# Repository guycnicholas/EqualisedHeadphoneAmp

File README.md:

# EqualisedHeadphoneAmp
These are the design files (Eagle, Spice, and an Excel spreadsheet) required for my Instructable: Equalised Headphone Amp

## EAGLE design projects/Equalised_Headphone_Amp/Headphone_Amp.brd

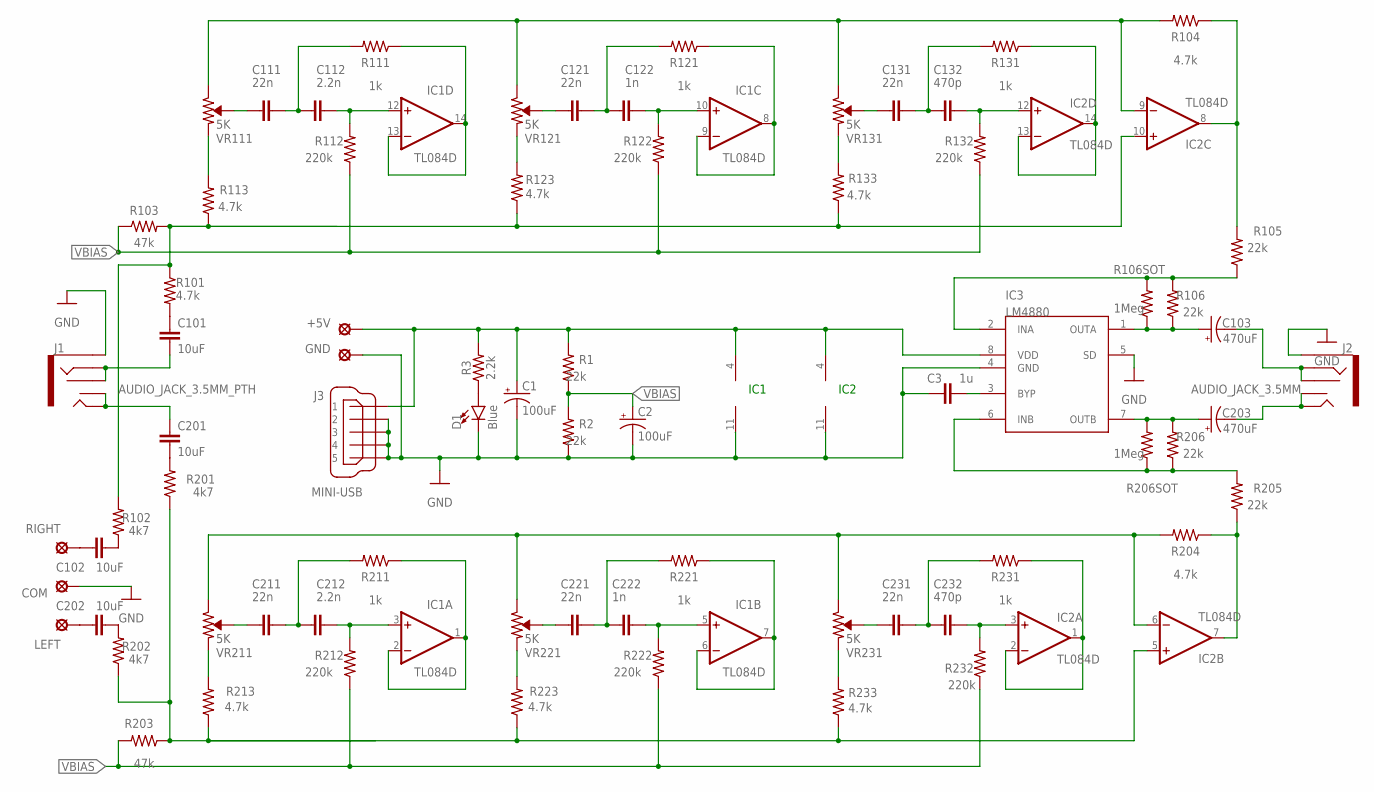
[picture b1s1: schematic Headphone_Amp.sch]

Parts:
+5V: SE14
C1, C2: 100uF; EIA7343
C3: 1u; 0603
C101, C102, C201, C202: 10uF; 0805
C103, C203: 470uF; EIA7343
C111, C121, C131, C211, C221, C231: 22n; 0603
C112, C212: 2.2n; 0603
C122, C222: 1n; 0603
C132, C232: 470p; 0603
COM: SE14
D1: Blue; LED_3MM
GND: SE14
IC1, IC2: TL084D; SO14
IC3: LM4880; SO08
J1: AUDIO_JACK_3.5MM_PTH; AUDIO-JACK
J2: AUDIO_JACK_3.5MM; AUDIO-JACK
J3: MINI-USB; UX60A-MB-5ST
LEFT: SE14
R1, R2, R105, R106, R205, R206: 22k; 0603
R3: 2.2k; 0603
R101, R104, R113, R123, R133, R204, R213, R223, R233: 4.7k; 0603
R102, R201, R202: 4k7; 0603
R103, R203: 47k; 0603
R106SOT, R206SOT: 1Meg; AXIAL-0.3
R111, R121, R131, R211, R221, R231: 1k; 0603
R112, R122, R132, R212, R222, R232: 220k; 0603
RIGHT: SE14
VR111, VR121, VR131, VR211, VR221, VR231: 5K; TRIMPOT-PTH-3362P

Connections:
GND: C1.C (-), C2.C (-), C3.1, COM.MP, D1.K (C), GND.MP, IC1.11 (V-), IC2.11 (V-), IC3.4 (GND), IC3.5 (SD), J1.SLEEVE, J2.SLEEVE, J3.2, J3.3, J3.4, J3.5, R2.1
HDPHNE: C103.C (-), J2.RING, J2.RSH
IN_L: C201.1, J1.TIP, J1.TSH
unnamed: C101.2, J1.RING, J1.RSH
unnamed: D1.A, R3.1
unnamed: C3.2, IC3.3 (BYP)
unnamed: C111.2, C112.1, R111.2
unnamed: C112.2, IC1.12 (+IN), R112.2
unnamed: IC1.1 (OUT), IC1.2 (-IN), R211.1
unnamed: C111.1, VR111.2 (WIPER)
unnamed: C203.C (-), J2.TIP, J2.TSH
unnamed: C121.2, C122.1, R121.2
unnamed: C122.2, IC1.10 (+IN), R122.2
unnamed: C201.2, R201.2
unnamed: R113.2, VR111.1 (CCW)
unnamed: C131.2, C132.1, R131.2
unnamed: C132.2, IC2.12 (+IN), R132.2
unnamed: C121.1, VR121.2 (WIPER)
unnamed: IC3.2 (INA), R105.1, R106.2, R106SOT.P$2 (2)
unnamed: C103.A (+), IC3.1 (OUTA), R106.1, R106SOT.P$1 (1)
unnamed: IC3.6 (INB), R205.2, R206.1, R206SOT.P$1 (1)
unnamed: C203.A (+), IC3.7 (OUTB), R206.2, R206SOT.P$2 (2)
unnamed: R123.2, VR121.1 (CCW)
unnamed: C211.2, C212.1, R211.2
unnamed: C212.2, IC1.3 (+IN), R212.2
unnamed: R213.2, VR211.1 (CCW)
unnamed: IC1.6 (-IN), IC1.7 (OUT), R221.1
unnamed: IC2.1 (OUT), IC2.2 (-IN), R231.1
unnamed: IC2.9 (-IN), R104.2, VR111.3 (CW), VR121.3 (CW), VR131.3 (CW)
unnamed: C221.2, C222.1, R221.2
unnamed: C222.2, IC1.5 (+IN), R222.2
unnamed: C211.1, VR211.2 (WIPER)
unnamed: IC2.6 (-IN), R204.2, VR211.3 (CW), VR221.3 (CW), VR231.3 (CW)
unnamed: C231.2, C232.1, R231.2
unnamed: C232.2, IC2.3 (+IN), R232.2
unnamed: R223.2, VR221.1 (CCW)
unnamed: IC1.8 (OUT), IC1.9 (-IN), R121.1
unnamed: R133.2, VR131.1 (CCW)
unnamed: IC2.10 (+IN), R101.1, R102.2, R103.2, R113.1, R123.1, R133.1
unnamed: +5V.MP, C1.A (+), IC1.4 (V+), IC2.4 (V+), IC3.8 (VDD), J3.1, R1.2, R3.2
unnamed: C101.1, R101.2
unnamed: IC1.13 (-IN), IC1.14 (OUT), R111.1
unnamed: C131.1, VR131.2 (WIPER)
unnamed: IC2.13 (-IN), IC2.14 (OUT), R131.1
unnamed: C221.1, VR221.2 (WIPER)
unnamed: C231.1, VR231.2 (WIPER)
unnamed: R233.2, VR231.1 (CCW)
unnamed: C102.1, RIGHT.MP
unnamed: C202.1, LEFT.MP
unnamed: C202.2, R202.2
unnamed: C102.2, R102.1
unnamed: IC2.5 (+IN), R201.1, R202.1, R203.1, R213.1, R223.1, R233.1
OUT-R: IC2.8 (OUT), R104.1, R105.2
OUT_L: IC2.7 (OUT), R204.1, R205.1
VBIAS: C2.A (+), R1.1, R2.2, R103.1, R112.1, R122.1, R132.1, R203.2, R212.1, R222.1, R232.1

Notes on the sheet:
IC1
IC2

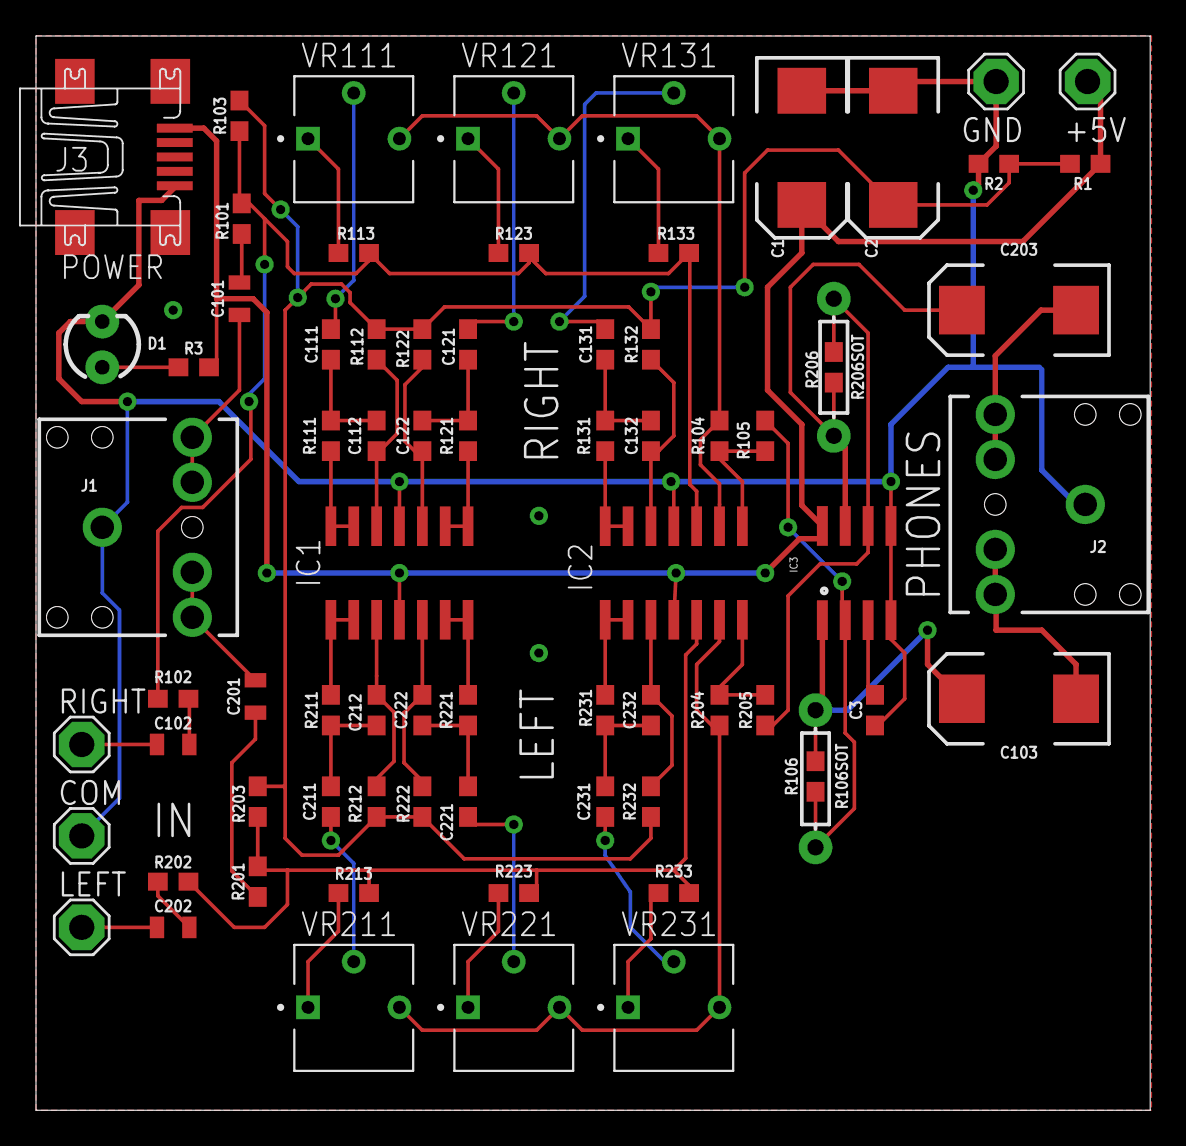
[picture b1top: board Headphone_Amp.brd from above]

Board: 2 copper layers, 61.9 x 59.7 mm, 74 parts (0 on the bottom side), 55 nets.

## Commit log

2023-10-01 Initial unzipped

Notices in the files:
parts and their libraries:
SparkFun-Capacitors: Licensing: Creative Commons ShareAlike 4.0 International - https://creativecommons.org/licenses/by-sa/4.0
